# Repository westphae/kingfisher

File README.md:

# Kingfisher

Kingfisher is a flight data recorder for light aircraft. It runs on a
Raspberry Pi mounted in the cabin, reads sensors over IIO and ancillary
links, derives quantities like pressure altitude, magnetic declination,
and an AHRS-based attitude estimate, persists everything to a SQLite
flight database, and exposes a live cockpit UI over HTTP/WebSocket.

## Hardware

* **Main unit** mounted near the aircraft CG, inside the cabin.
  * Main controller is a `Raspberry Pi 5`.
  * Accel/gyro is a `ICM45686`.
  * GPS is a `NEO-M9N` attached via UART.
* **Pod unit** mounted out under the wing.
  * Pod controller is an `ESP32-C3-Mini-1`, variant `ESP32-C3FH4`.
  * Airspeed sensor is a `MS4525DO-DS5AI001DP`.
  * Static pressure (altimeter) sensor is a `BMP581`.
  * Magnetometer (compass) sensor is a `MMC5983MA`.

The pod is battery-powered and transmits sensor data to the main unit
wirelessly. See `internal/pod/` (Pi side) and `firmware/pod/` (ESP32
side) for the implementation.

## GPS

The `NEO-M9N` is wired to the Pi 5's GPIO UART (GPIO 14/15, header pins
8/10), enabled by `dtoverlay=uart0-pi5` in `/boot/firmware/config.txt`.

Kingfisher assumes the host wall clock is already sane. For offline operation,
discipline the Pi with `gpsd` + `chrony` first; see `docs/time-sync.md`.

**Pi 5 gotcha:** that UART is `/dev/ttyAMA0`, *not* `/dev/serial0`. On a
Pi 5 `/dev/serial0` points at the dedicated 3-pin debug-UART connector
(`ttyAMA10`), so gpsd must be told to use `/dev/ttyAMA0`. In
`/etc/default/gpsd`:

```
DEVICES="/dev/ttyAMA0"
GPSD_OPTIONS="-n -b -s 115200"
```

The `-b` (read-only) flag is deliberate. If you configured the M9N for 115200 baud
(saved to flash), you must also pass `-s 115200`; with `-b`, gpsd will not autobaud
and otherwise opens the port at 19200, which produces no fix and no TPV output. Left to manage the receiver,
gpsd subscribes a heavy set of UBX messages (NAV-SAT/SIG/POSECEF/…) that
saturate the link and drop the effective fix rate. Read-only keeps the
lean NAV-PVT-only stream the receiver is configured to emit, so we get a
clean 10 Hz.

For time discipline, prefer chrony's SOCK integration over SHM and keep
`chronyd` ahead of `gpsd` in the service order (and restart `gpsd` after any
`chronyd` restart). The repo-owned examples live in `deploy/time-sync/`. With PPS
wired, PPS disciplines the clock and the GPS serial source is marked `noselect`
(time-of-day only) — no per-receiver `offset` tuning is needed. See
`docs/time-sync.md`.

The receiver itself is configured once with `ubxtool` and the settings
are saved to its flash (they survive power-off). With gpsd running:

```bash
export UBXOPTS="-P 32.01"                      # M9N protocol version
ubxtool -z CFG-NAVSPG-DYNMODEL,7,7             # Airborne <2g (vs 0=portable)
ubxtool -z CFG-RATE-MEAS,100,7                 # 10 Hz (100 ms)
ubxtool -z CFG-RATE-NAV,1,7                    # 1 nav solution per measurement
```

To bump the link to 115200 and emit only UBX-NAV-PVT (do this with gpsd
*stopped*, talking to the port directly), set `CFG-UART1-BAUDRATE` to
`115200`, `CFG-MSGOUT-UBX_NAV_PVT_UART1` to `1`, and the other
`CFG-MSGOUT-UBX_NAV_*_UART1` items to `0`. The `,7` layer suffix writes
RAM+BBR+Flash so the config persists. The **Airborne dynamic model is the
most important setting** — the factory "portable" default filters motion
in ways that lag or drop fixes during climbs, descents, and turns.

### Rate (5 / 10 Hz)

The receiver always runs at 10 Hz; the GPS tab in the cockpit UI selects
the **recorded** rate (`rate_hz`, 5 or 10). Because gpsd is read-only,
kingfisher doesn't reconfigure the receiver — it decimates the 10 Hz
stream in software (`internal/gps`), publishing/recording every fix at
10 Hz or every other fix at 5 Hz. The setting persists in
`config.json` under `gps.rate_hz`.

### Timestamps (`ts_ns` vs fix time)

Each row in the `gps` table (and every other sensor table) has **`ts_ns`**: nanoseconds
on the Pi's disciplined wall clock. For GPS, **`ts_ns` is not the fix epoch** — it
is when kingfisher **received** the gpsd report. The receiver's fix time is stored
separately as the **`fix_time_unix_s`** column (typically **~600–700 ms earlier**
than `ts_ns` on this M9N + gpsd setup; that gap is receiver/pipeline lag, not clock
error).

For sensor fusion: align GPS with cabin IMU and pod data on **`ts_ns`**; use
**`fix_time_unix_s`** when you need GNSS solution time. Full per-source semantics
(buffered IIO, pod reconstruction, derived devices, fusion checklist) are in
**[`docs/timestamps.md`](docs/timestamps.md)**.

## Timestamps

All flight DB sensor tables store **`ts_ns`** (nanoseconds, Unix epoch) on the
Pi host wall clock (`CLOCK_REALTIME`), ideally GNSS-disciplined before recording.

| Source | `ts_ns` meaning (summary) |
|--------|---------------------------|
| Buffered IIO (ICM45686, …) | Kernel capture time when `current_timestamp_clock == realtime` |
| Polled IIO | Time when the periodic sysfs read completed |
| GPS | Pi time when the TPV was **received**; fix epoch is **`fix_time_unix_s`** |
| Pod (BMP581, MS4525, MMC5983) | Sample time reconstructed onto Pi clock from pod uptime + `age_us` |
| Derived (AHRS, press_alt, geo, compass) | Time when the value was **computed** (inputs may be slightly older) |

See **[`docs/timestamps.md`](docs/timestamps.md)** for measurement error vs true
sample time, GPS fusion guidance, and implementation references.

## Engine data (JPI EDM-930)

The EDM-930 is not on the live bus. After the flight, merge one download
into the flight SQLite. This installation records no altitude and no second
TIT, so the match is the GPS ground track. Format, refusal rules, and the
`jpi_edm930` columns are in [`docs/jpi-edm930.md`](docs/jpi-edm930.md).

```bash
uv run --project analysis python scripts/analyze_flights.py jpi \
  --jpi PATH/TO/FILE.JPI \
  --db PATH/TO/FLIGHT.sqlite \
  --flight N
```

That command is a dry run. Add `--apply` to write. Do not commit the `.jpi`
file or the flight database.

## Building

```
go build ./cmd/kingfisher
```

Pod firmware lives under `firmware/pod/`; see
[`firmware/pod/README.md`](firmware/pod/README.md) for the wiring,
toolchain, and flashing steps.

## Lint hook

Once per clone:

```bash
scripts/install-git-hooks.sh
```

That sets `git config core.hooksPath .githooks`. The pre-commit hook runs
`scripts/lint.sh`: `gofmt` on staged Go files, `scripts/check-wire.sh` when
`pod_wire/` or `internal/pod/wire/` is staged or those trees have unstaged
drift, and `golangci-lint` only if it is already on `PATH`. `gofmt` and the
wire check fail the commit. Unchecked `Close`, `Rollback`, and deadline
setters are ignored in `.golangci.yml`.

## Running

```
./kingfisher
```

Kingfisher listens on **`http_addr`** (default **`:8080`**) and is meant to sit
behind a reverse proxy on the aircraft LAN. Configuration lives in
`~/.config/kingfisher/config.json`.

### HTTPS with Caddy (recommended)

[Caddy](https://caddyserver.com/) terminates TLS on port **443**, redirects HTTP
port **80** to HTTPS, and reverse-proxies to kingfisher on `localhost:8080`
(including WebSocket traffic for the live cockpit and `/terminal`).

Example Caddyfile (also in **`deploy/caddy/Caddyfile`**). Adjust the hostname and
LAN IP for your Pi:

```caddyfile
https://kingfisher.lan, https://kingfisher, https://192.168.10.1, https://192.168.86.151, https://127.0.0.1 {
    tls internal
    reverse_proxy localhost:8080
}

http://kingfisher.lan, http://kingfisher, http://192.168.10.1, http://192.168.86.151, http://127.0.0.1 {
    redir https://{host}{uri} permanent
}
```

`tls internal` uses a **local certificate authority** managed by Caddy — fine for
a private LAN; not a public-trusted cert.

**Install on Debian / Raspberry Pi OS** (official apt repo):

```bash
sudo apt install -y debian-keyring debian-archive-keyring apt-transport-https curl
curl -1sLf 'https://dl.cloudsmith.io/public/caddy/stable/gpg.key' \
  | sudo gpg --dearmor -o /usr/share/keyrings/caddy-stable-archive-keyring.gpg
curl -1sLf 'https://dl.cloudsmith.io/public/caddy/stable/debian.deb.txt' \
  | sudo tee /etc/apt/sources.list.d/caddy-stable.list
sudo chmod o+r /usr/share/keyrings/caddy-stable-archive-keyring.gpg \
  /etc/apt/sources.list.d/caddy-stable.list
sudo apt update && sudo apt install -y caddy
sudo cp deploy/caddy/Caddyfile /etc/caddy/Caddyfile
sudo caddy validate --config /etc/caddy/Caddyfile
sudo systemctl enable --now caddy
```

Keep kingfisher on the loopback port only:

```json
"http_addr": ":8080"
```

**Trust the CA**

On the Pi (so curl and local browsers trust HTTPS):

```bash
sudo caddy trust
```

On laptops, phones, and tablets, install Caddy's root certificate once. After
Caddy has started at least once, the file is usually:

```text
/var/lib/caddy/.local/share/caddy/pki/authorities/local/root.crt
```

Copy it to the device and add it to the system/browser trust store (or use
`sudo caddy trust` on each Linux machine). Until then, browsers show a
certificate warning — you can proceed for testing, but trusting the CA removes
the nag and enables secure-context APIs (clipboard, etc.) over HTTPS.

Open the cockpit at **`https://<pi-hostname-or-ip>/`** (port 443; HTTP on port 80
redirects automatically).

### EFB apps (ForeFlight, iFlyEFB)

Kingfisher can broadcast **Stratux-compatible GDL90** over UDP port **4000** so
tablets on the Pi access point receive GPS position and AHRS attitude without a
separate Stratux box. Enable in `config.json`:

```json
"gdl90": {
  "enabled": true,
  "static_ips": ["192.168.10.141", "192.168.10.40"]
}
```

On the Pi AP (NetworkManager + dnsmasq), list each tablet’s reserved IP in
`static_ips` — see **`deploy/efb/ap-setup.md`** for DHCP reservations, MAC
privacy settings, and verification.

**ForeFlight:** connect to the Pi Wi‑Fi → *More* → *Devices* → enable GDL90 at
**`192.168.10.1`**.

**iFlyEFB:** *Menu* → *About* → *Connected Devices* → Stratux/FlightBox;
*Setup* → *ADS-B* → Stratux/Flightbox (manual). Expect **GPS Data Only**.

Requires `ahrs.enabled` for attitude. Traffic and weather are not sent (no ADS-B
receiver). Check `/api/status` → `gdl90` for client count and last send time;
`tcpdump -i wlan0 udp port 4000` should show steady packets when an EFB is
connected.

### systemd user service (boot)

Kingfisher is normally run as your Pi login user (IIO device access, config under
`~/.config/kingfisher/`, flight DBs under `~/kingfisher/flights`). A **systemd user
unit** starts it at boot without keeping an SSH session open.

**Prerequisites:** gpsd and chrony configured per **`docs/time-sync.md`**. If you
use Caddy for HTTPS, enable **`caddy.service`** separately (system unit); start
kingfisher first so the reverse proxy has a backend on `:8080`.

1. **Install the binary** with `go install` (default: `$(go env GOPATH)/bin`, usually
   `~/go/bin`; override with `GOBIN` if you use it):

   ```bash
   cd ~/go/src/github.com/westphae/kingfisher
   go install ./cmd/kingfisher
   ```

2. **Install the user unit** from the repo example (path must match step 1):

   ```bash
   mkdir -p ~/.config/systemd/user
   bin="$(go env GOBIN)"
   [ -z "$bin" ] && bin="$(go env GOPATH)/bin"
   sed "s|__KINGFISHER_BIN__|$bin/kingfisher|g" \
     deploy/systemd/kingfisher.service.example \
     > ~/.config/systemd/user/kingfisher.service
   ```

3. **Enable linger** so the user service starts at boot (not only after login):

   ```bash
   sudo loginctl enable-linger "$USER"
   loginctl show-user "$USER" -p Linger   # expect Linger=yes
   ```

4. **Enable and start:**

   ```bash
   systemctl --user daemon-reload
   systemctl --user enable --now kingfisher.service
   ```

5. **Check status and logs:**

   ```bash
   systemctl --user status kingfisher.service
   journalctl --user-unit=kingfisher.service -f
   curl -s http://127.0.0.1:8080/api/status | head
   ```

   Use **`--user-unit`** (not `journalctl --user`): on Raspberry Pi OS the user
   manager logs to the **system** journal; there is no separate per-user journal
   file under `/run/user/$UID/journal`, so `journalctl --user` shows nothing even
   though `systemctl --user status` does.

The unit starts kingfisher **immediately** — there is no chrony pre-wait (the
old `kingfisher-prestart.sh` gate is retired). The UI and recording come up in
seconds on the RTC clock:

| Situation | Behavior |
|-----------|----------|
| **RTC sane (normal)** | Timestamp-named flight DB; red cockpit banner until chrony locks |
| **Any chrony step/slew ≥ 20 ms** | Row in the DB's `clock_offsets` table (see `docs/timestamps.md`) |
| **RTC dead (clock reads 1970)** | DB named `unsynced_NNNN_<tail>.db`; renamed at close once true time is known |

Startup metadata, the `clock_offsets` mapping table, and the cockpit clock
badge/banner record discipline state. `RestartSec=30` retries a failed main
process.

**After upgrading:** `go install ./cmd/kingfisher`, then
`systemctl --user restart kingfisher.service`.

**Stop/disable:**

```bash
systemctl --user disable --now kingfisher.service
```

Example unit file: **`deploy/systemd/kingfisher.service.example`**.

### Browser terminal (optional)

Kingfisher can expose a full-screen web terminal at **`/terminal`** (footer link
on the cockpit page). It is **disabled by default**; enable in `config.json`:

```json
"terminal": {
  "enabled": true,
  "user": "eric",
  "authorized_keys": [
    "ssh-ed25519 AAAA... kingfisher-terminal"
  ],
  "allow_password": false,
  "session_timeout_min": 480,
  "max_sessions": 2
}
```

**Public-key login (recommended):** put one or more OpenSSH `authorized_keys` lines in
`authorized_keys` and set `user` to the Unix account the shell should run as. The
browser signs a one-time challenge with a private key stored locally (generate in
the terminal UI, or import an unencrypted Ed25519 `id_ed25519`). Your password is
never sent. Set `"allow_password": true` to keep PAM login as a fallback.

**Password login:** when `authorized_keys` is omitted, login uses **Linux PAM**
(same username/password as SSH). The shell runs as the authenticated user when
kingfisher runs as that user; logging in as a different user requires root or
`cap_setuid` on the kingfisher binary.

**Security:** with Caddy **`tls internal`** in front (see above), terminal traffic
including WebSockets is encrypted on the LAN. Without HTTPS, password login sends
credentials in cleartext; public-key login avoids sending passwords but session
cookies and shell I/O are still visible on the wire.

Building on Linux requires **`libpam0g-dev`** for CGO (`apt install libpam0g-dev`).

If you want DB filenames, session start times, and buffered IIO timestamps to be
meaningful immediately after boot, start kingfisher only after GNSS time sync is
healthy. `docs/time-sync.md` includes a `chronyc waitsync` systemd pattern and a
verification checklist. Per-table **`ts_ns`** semantics and sensor-fusion usage
(including GPS **`fix_time_unix_s`**) are documented in **`docs/timestamps.md`**.

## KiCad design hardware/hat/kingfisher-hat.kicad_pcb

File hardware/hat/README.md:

# Kingfisher Sensor HAT (rev 0.3)

Custom HAT for the extra-tall GPIO header above the M.2 HAT+. It replaces the
cabin SparkFun NEO-M9N and ICM-45686 breakouts. The schematic netlist is
checked. The board is routed on JLCPCB stackup JLC04161H-7628. Gerbers
and drills are in `fab/`. Confirm header engagement, the CR2032 against the
lid, and that the GNSS antenna is active before ordering.

| Ref | Part | Role |
|-----|------|------|
| U1 | ICM-45686 | Cabin IMU, I²C `0x68`, INT1 → GPIO17 |
| U2 | BMP581 | Extra cabin baro, I²C `0x47` |
| U3 | AP2112K-3.3 | 5 V → 3.3 V for the GPS only |
| U4 | NEO-M9N | GNSS, UART0 + PPS on GPIO18 |
| U5 | RV-3028-C7 | I²C RTC at `0x52` |
| U6 | LM4040-3.0 | 3.00 V clamp for the ML414H charge |
| BT1 | CR2032, Keystone 3002 | Replaceable cell for the RTC `VBACKUP` only |
| BT2 | ML414H | Soldered rechargeable cell on GPS `V_BCKP` |
| D1 | PMEG4005EJ | Blocks the ML414H from the reference |
| D2 | Green LED | `+3V3_GPS` through 1 kΩ |
| D3 | ESD0P2RF | 0.2 pF ESD diode, RF to ground at the U.FL |
| L1 | LQG15HS27NJ02D | 27 nH antenna-bias choke |
| J1 | 2×20 socket, bottom | Mates the extended Pi header. Do not move it |
| J2 | U.FL | Antenna. 0.32 mm microstrip plus the bias-T stub |
| J3 | 1×5 header | X1200 harness: +3V3, GND, SDA, SCL, GPIO6 |

Outline is the official Pi HAT (65 × 56.5 mm, M2.5 on 58 × 49 mm).

The GPS circuit follows UBX-19014285 and UBX-19014286: `V_USB` grounded,
UART pull-up on `D_SEL`, 33 Ω on TX/RX, ML414H directly on `V_BCKP` charged
through an LM4040-3.0 and 34 kΩ, and a 27 nH / 100 nF bias-T into the
antenna. The CR2032 does not back up the GPS and has no charge path. There
is no UPS on this board. See [docs/DESIGN.md](docs/DESIGN.md).

## Open in KiCad

KiCad 9 (generated against 9.0.2).

```bash
kicad hardware/hat/kingfisher-hat.kicad_pro
```

Libraries:

- `libs/Kingfisher.kicad_sym` — ICM-45686, BMP581, NEO-M9N
- `libs/Kingfisher.pretty` — ICM-45686 (TDK pin numbers), BMP581, ML414H

Regenerate with system Python, not a uv venv. `pcbnew` comes from
`python3-pcbnew`.

```bash
python3 hardware/hat/scripts/build_libs.py
python3 hardware/hat/scripts/build_sch.py
kicad-cli sch export netlist -o /tmp/kingfisher-hat.net hardware/hat/kingfisher-hat.kicad_sch
python3 hardware/hat/scripts/check_netlist.py /tmp/kingfisher-hat.net
python3 hardware/hat/scripts/place_pcb.py
python3 hardware/hat/scripts/route_pcb.py
```

`check_netlist.py` is the schematic check. It passed for rev 0.3 (69 nets).
`place_pcb.py` keeps the template socket and mounting holes and deletes
tracks. `route_pcb.py` restores the route and the 4-layer stackup.

## Status

Done:

- Schematic for the GPS replica, TDK IMU land, BMP581, RV-3028, both backup
  cells, X1200 header, test points, and the GPS power LED
- Netlist check against datasheet pin numbers
- Parts placed on the HAT outline, clear of the notch, the slot, the mounting
  holes, and the header
- Routed, including the 0.32 mm U.FL microstrip (bare Z0 about 50.2 Ω at the
  pressed 7.1 mil / Er 4.4 height). Soldermask pulls that down about 1–2 Ω
- JLC04161H-7628 stackup filled in. Error-level DRC is clean
- Gerbers and drills in `fab/`

Still to confirm on the aircraft, and still open in software:

- Female-header engagement, lid clearance over the CR2032, pin 1 against the
  real extender, and whether the GNSS antenna is active
- `i2c-rtc` for the RV-3028, a cabin BMP581 reader, and an AHRS mount matrix
  measured from this board's silk

## Attribution

- Outline and GPIO socket: KiCad Raspberry Pi HAT template
- BMP581 pads: SparkFun Qwiic BMP581 hardware, CC-BY-SA 4.0
- ML414H pads and the GPS power circuit: SparkFun NEO-M9N SMA / SparkFun-Batteries
- NEO-M9N symbol: derived from the KiCad `NEO-M8N` symbol
- ICM-45686 pad centers: IPC LGA-14. Pin numbers and axes: TDK DS-000577

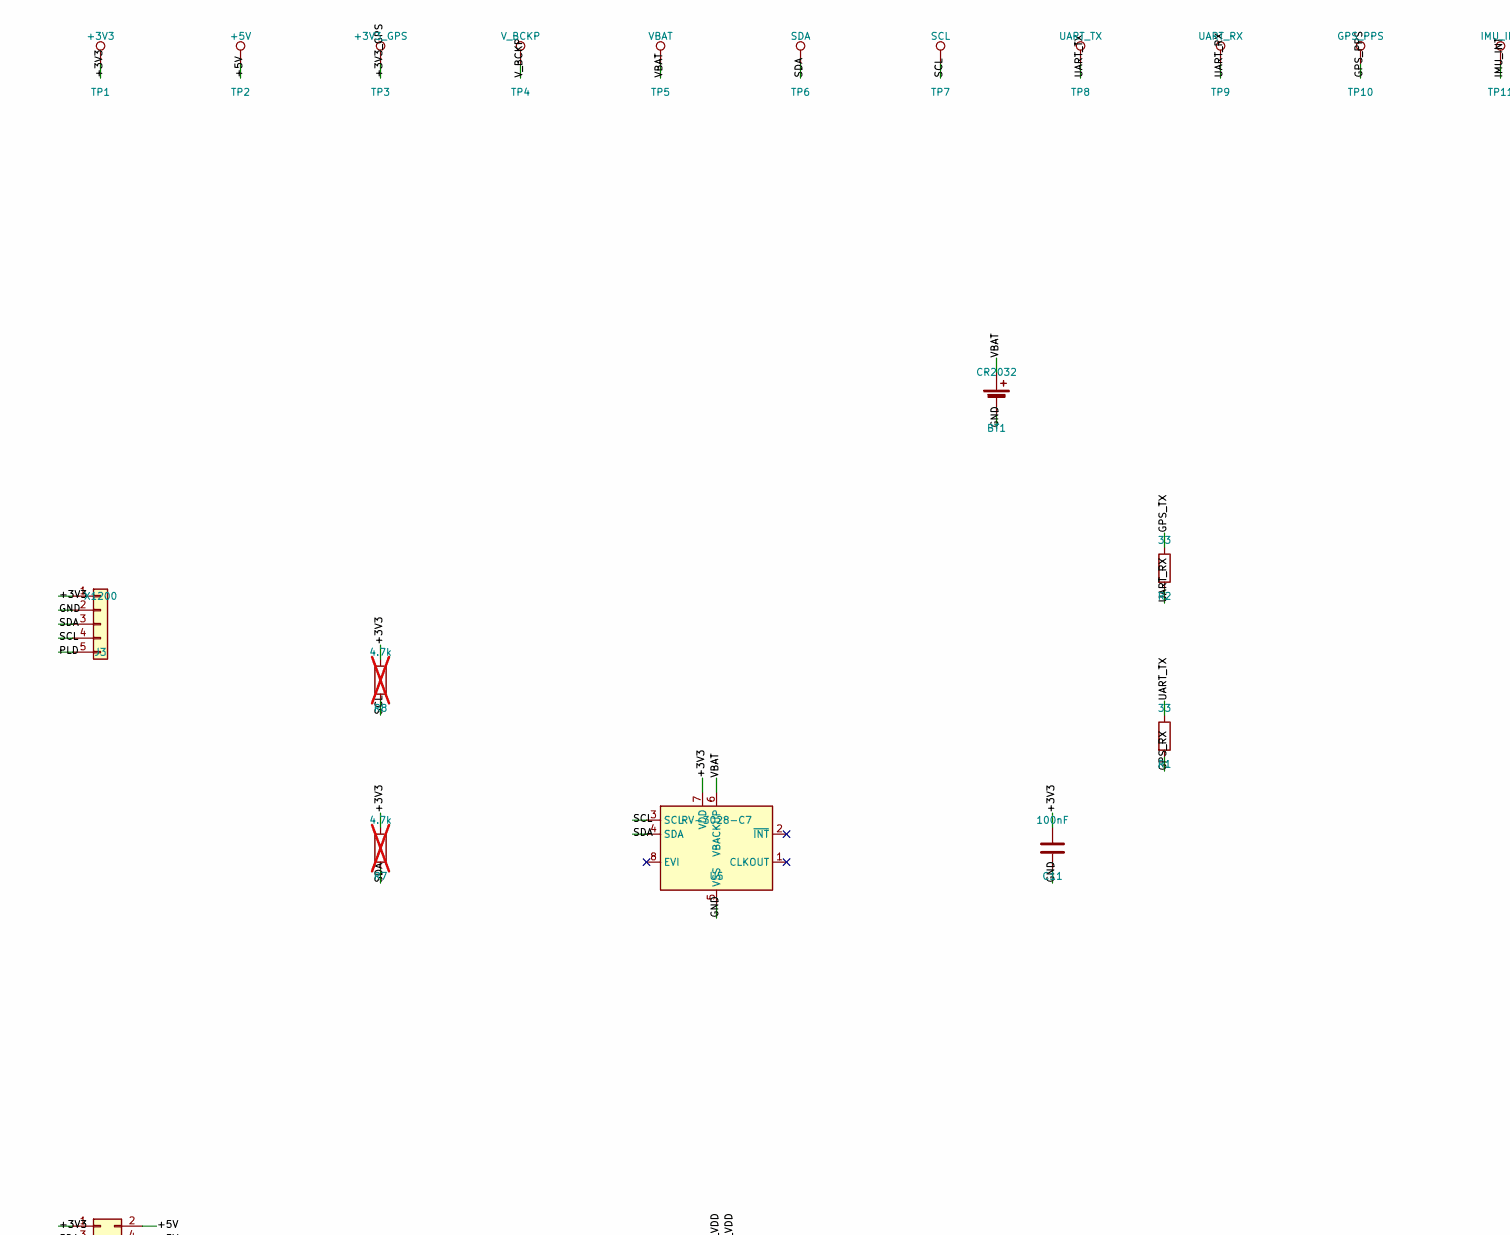
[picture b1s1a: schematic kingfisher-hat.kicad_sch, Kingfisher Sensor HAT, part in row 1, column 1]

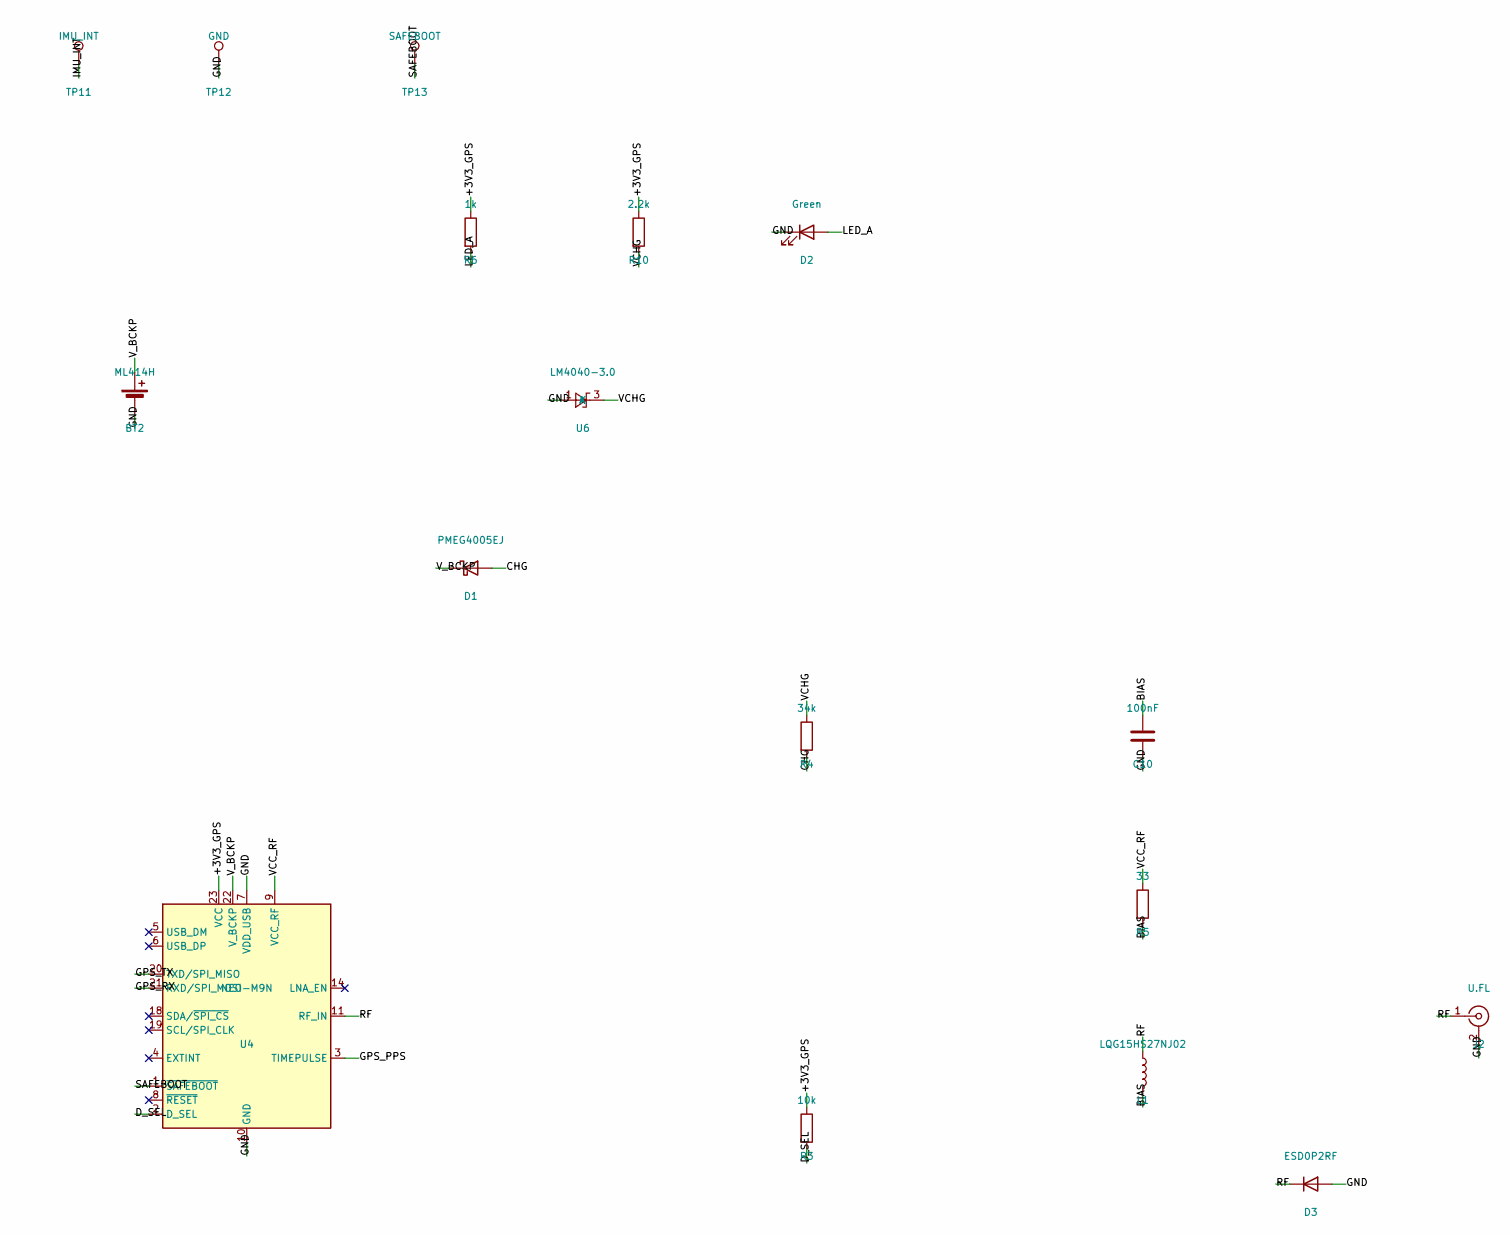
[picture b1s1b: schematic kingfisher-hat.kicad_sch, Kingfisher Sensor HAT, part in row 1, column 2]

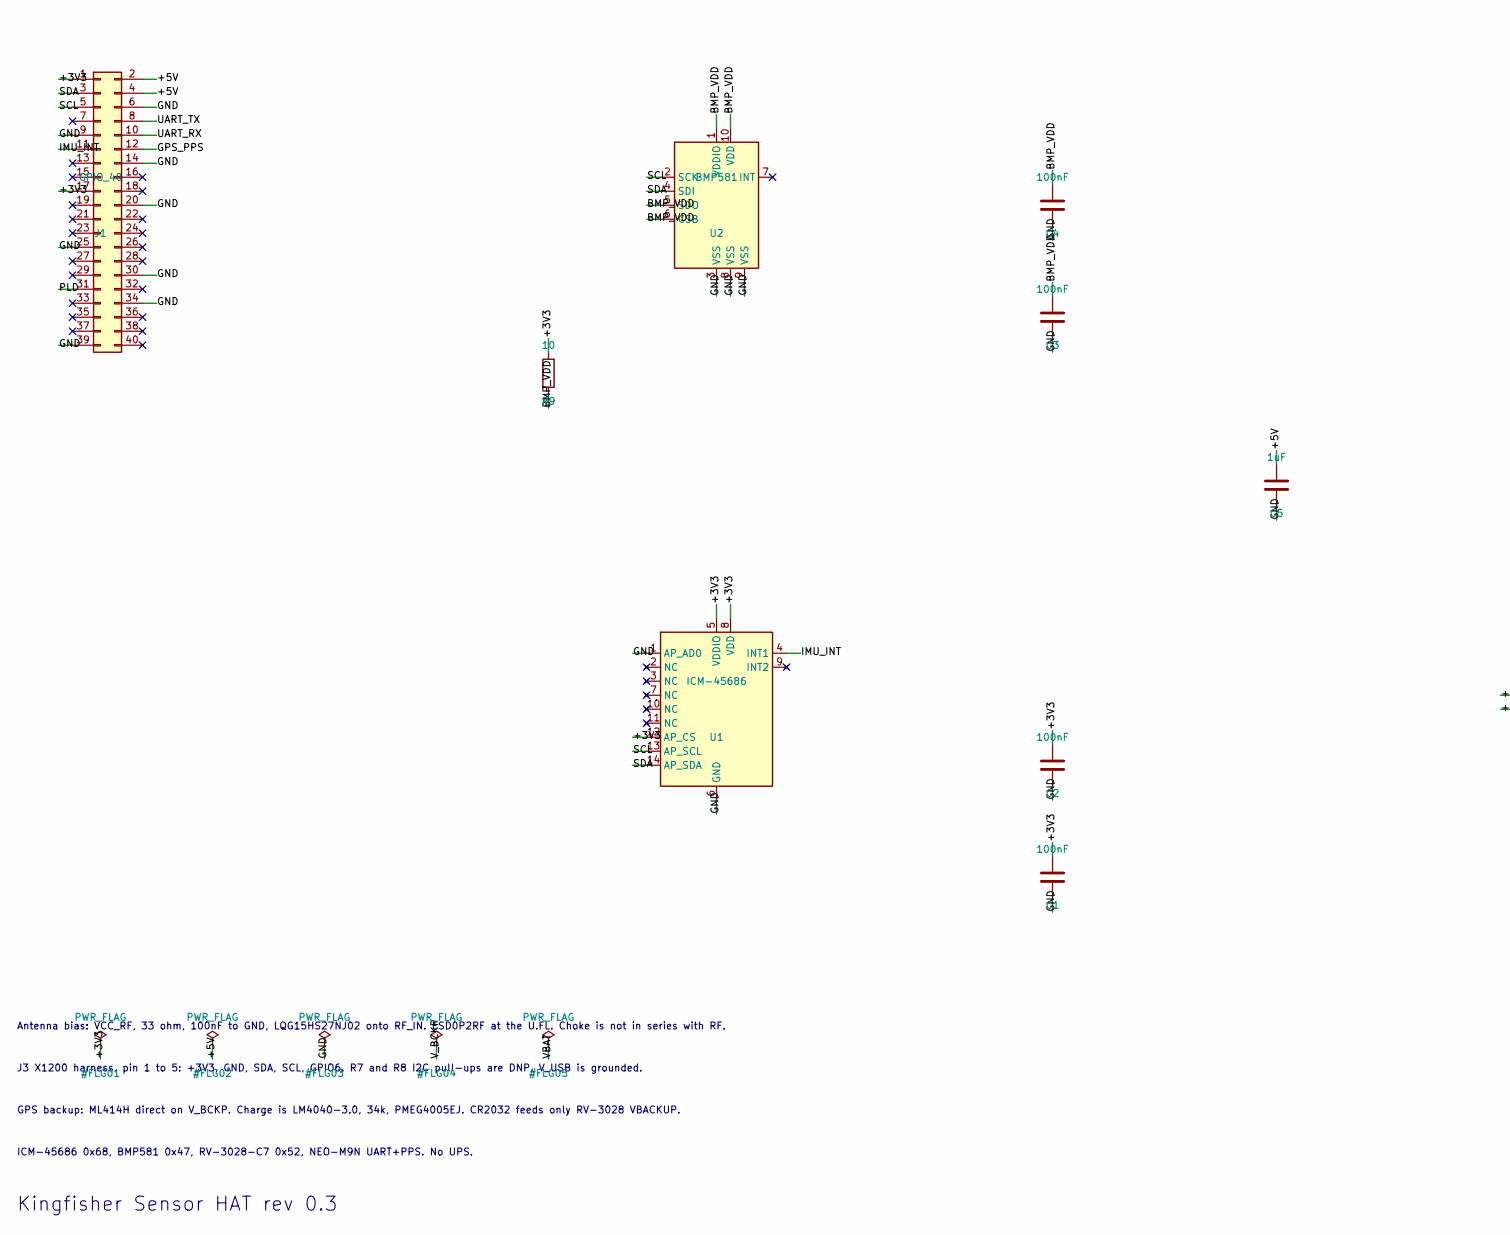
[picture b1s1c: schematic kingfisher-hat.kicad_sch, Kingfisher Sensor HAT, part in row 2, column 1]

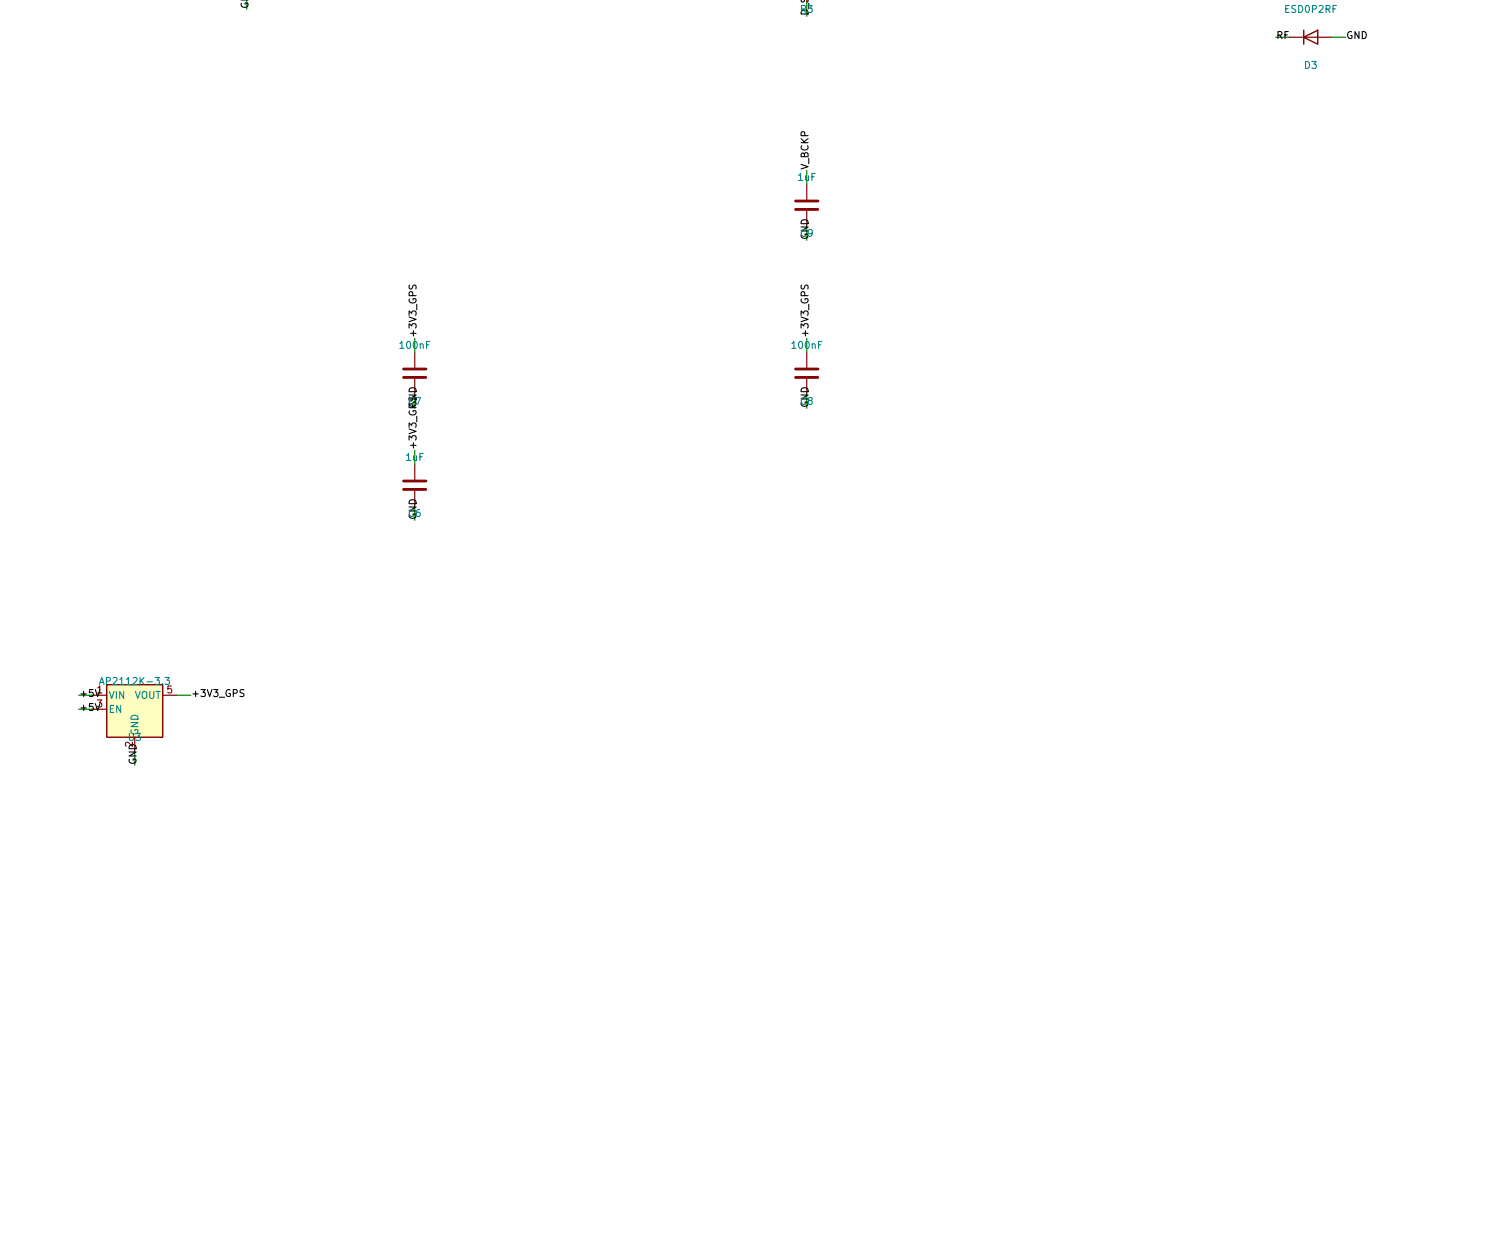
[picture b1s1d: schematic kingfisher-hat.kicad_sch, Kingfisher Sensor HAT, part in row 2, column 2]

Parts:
BT1: CR2032; BatteryHolder_Keystone_3002_1x2032
BT2: ML414H
C1, C2, C3, C4, C7, C8, C10, C11: 100nF; C_0402_1005Metric
C5, C6, C9: 1uF; C_0603_1608Metric
D1: PMEG4005EJ; D_SOD-323F
D2: Green; LED_0603_1608Metric
D3: ESD0P2RF; D_SOD-882
J1: GPIO_40; PinSocket_2x20_P2.54mm_Vertical
J2: U.FL; U.FL_Hirose_U.FL-R-SMT-1_Vertical
J3: X1200; PinHeader_1x05_P2.54mm_Horizontal
L1: LQG15HS27NJ02; L_0402_1005Metric
R1, R2: 33; R_0603_1608Metric
R3: 10k; R_0402_1005Metric
R4: 34k; R_0603_1608Metric
R5: 33; R_0402_1005Metric
R6: 1k; R_0603_1608Metric
R7, R8: 4.7k; R_0402_1005Metric; not fitted
R9: 10; R_0402_1005Metric
R10: 2.2k; R_0402_1005Metric
TP1: +3V3; TestPoint_Pad_D1.5mm
TP2: +5V; TestPoint_Pad_D1.5mm
TP3: +3V3_GPS; TestPoint_Pad_D1.5mm
TP4: V_BCKP; TestPoint_Pad_D1.5mm
TP5: VBAT; TestPoint_Pad_D1.5mm
TP6: SDA; TestPoint_Pad_D1.5mm
TP7: SCL; TestPoint_Pad_D1.5mm
TP8: UART_TX; TestPoint_Pad_D1.5mm
TP9: UART_RX; TestPoint_Pad_D1.5mm
TP10: GPS_PPS; TestPoint_Pad_D1.5mm
TP11: IMU_INT; TestPoint_Pad_D1.5mm
TP12: GND; TestPoint_Pad_D1.5mm
TP13: SAFEBOOT; TestPoint_Pad_D1.5mm
U1: ICM-45686
U2: BMP581
U3: AP2112K-3.3; SOT-23-5_JLC
U4: NEO-M9N; ublox_NEO
U5: RV-3028-C7; RV3028-C7_JLC
U6: LM4040-3.0; SOT-353_SC-70-5_JLC

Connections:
+3V3: C1.1, C2.1, C11.1, J1.1, J1.17, J3.1, R7.1, R8.1, R9.1, TP1.1, U1.5 (VDDIO), U1.8 (VDD), U1.12 (AP_CS), U5.7 (VDD)
+3V3_GPS: C6.1, C7.1, C8.1, R3.1, R6.1, R10.1, TP3.1, U3.5 (VOUT), U4.23 (VCC)
+5V: C5.1, J1.2, J1.4, TP2.1, U3.1 (VIN), U3.3 (EN)
BIAS: C10.1, L1.2, R5.2
BMP_VDD: C3.1, C4.1, R9.2, U2.1 (VDDIO), U2.5 (SDO), U2.6 (CSB), U2.10 (VDD)
CHG: D1.2 (A), R4.2
D_SEL: R3.2, U4.2 (D_SEL)
GND: BT1.2 (-), BT2.2 (-), C1.2, C2.2, C3.2, C4.2, C5.2, C6.2, C7.2, C8.2, C9.2, C10.2, C11.2, D2.1 (K), D3.2 (A), J1.6, J1.9, J1.14, J1.20, J1.25, J1.30, J1.34, J1.39, J2.2 (Ext), J3.2, TP12.1, U1.1 (AP_AD0), U1.6 (GND), U2.3 (VSS), U2.8 (VSS), U2.9 (VSS), U3.2 (GND), U4.7 (VDD_USB), U4.10 (GND), U4.12 (GND), U4.13 (GND), U4.24 (GND), U5.5 (VSS), U6.1 (A)
GPS_PPS: J1.12, TP10.1, U4.3 (TIMEPULSE)
GPS_RX: R1.2, U4.21 (RXD/SPI_MOSI)
GPS_TX: R2.1, U4.20 (TXD/SPI_MISO)
IMU_INT: J1.11, TP11.1, U1.4 (INT1)
LED_A: D2.2 (A), R6.2
PLD: J1.31, J3.5
RF: D3.1 (K), J2.1 (In), L1.1, U4.11 (RF_IN)
SAFEBOOT: TP13.1, U4.1 (~SAFEBOOT)
SCL: J1.5, J3.4, R8.2, TP7.1, U1.13 (AP_SCL), U2.2 (SCK), U5.3 (SCL)
SDA: J1.3, J3.3, R7.2, TP6.1, U1.14 (AP_SDA), U2.4 (SDI), U5.4 (SDA)
UART_RX: J1.10, R2.2, TP9.1
UART_TX: J1.8, R1.1, TP8.1
VBAT: BT1.1 (+), TP5.1, U5.6 (VBACKUP)
VCC_RF: R5.1, U4.9 (VCC_RF)
VCHG: R4.1, R10.2, U6.3 (K)
V_BCKP: BT2.1 (+), C9.1, D1.1 (K), TP4.1, U4.22 (V_BCKP)

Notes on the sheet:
Kingfisher Sensor HAT rev 0.3
ICM-45686 0x68, BMP581 0x47, RV-3028-C7 0x52, NEO-M9N UART+PPS. No UPS.
GPS backup: ML414H direct on V_BCKP. Charge is LM4040-3.0, 34k, PMEG4005EJ. CR2032 feeds only RV-3028 VBACKUP.
J3 X1200 harness, pin 1 to 5: +3V3, GND, SDA, SCL, GPIO6. R7 and R8 I2C pull-ups are DNP. V_USB is grounded.
Antenna bias: VCC_RF, 33 ohm, 100nF to GND, LQG15HS27NJ02 onto RF_IN. ESD0P2RF at the U.FL. Choke is not in series with RF.

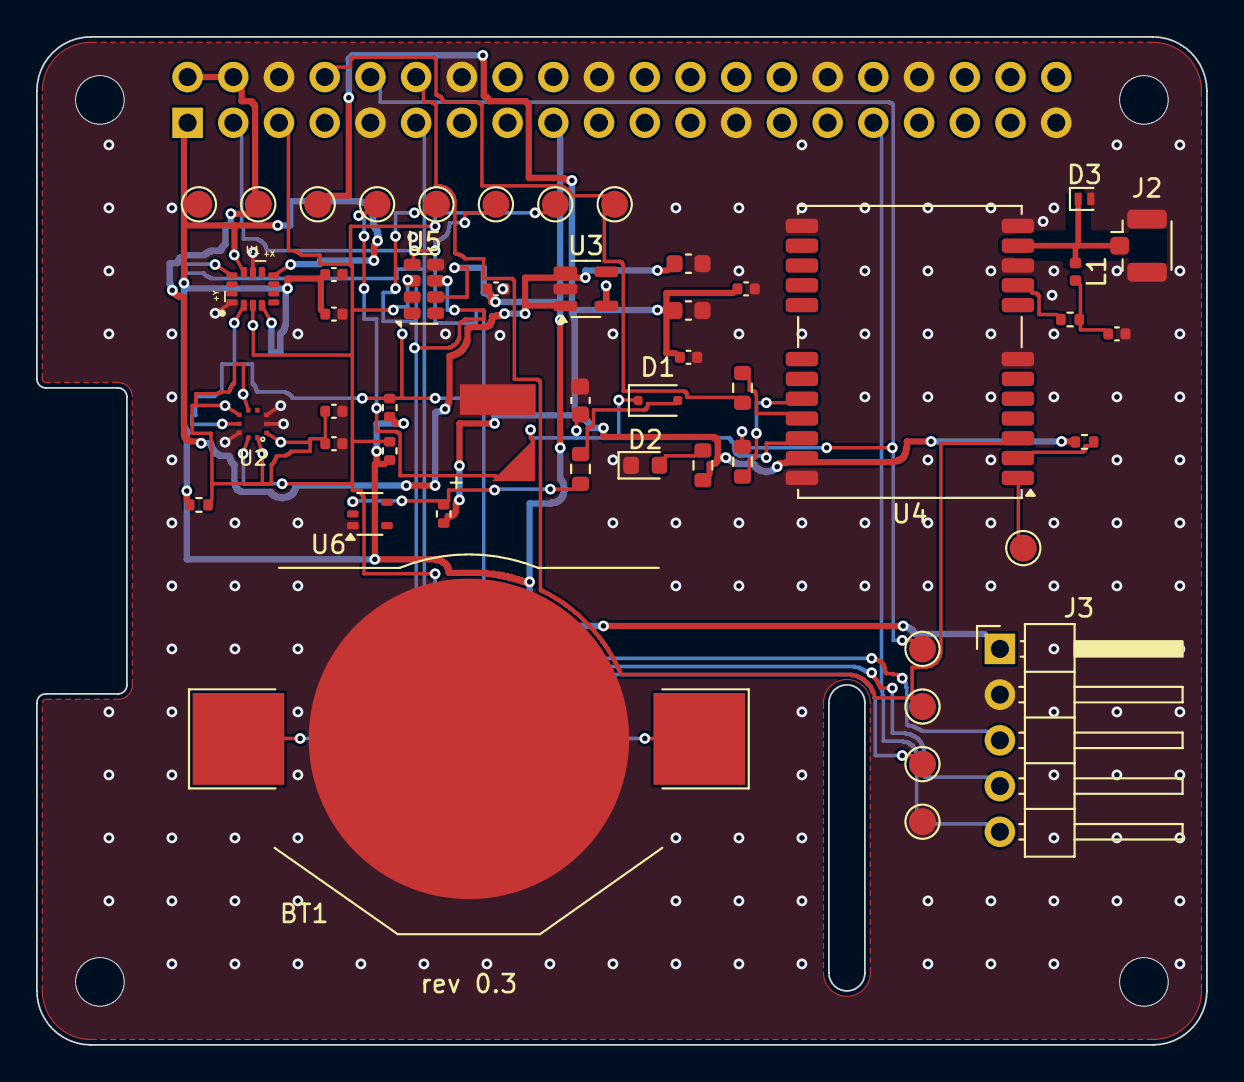
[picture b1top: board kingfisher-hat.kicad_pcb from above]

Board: 4 copper layers, 65.0 x 56.0 mm, 53 parts (1 on the bottom side), 24 nets.

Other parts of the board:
MH1, MH2, MH3, MH4: MountingHole_2.7mm_M2.5

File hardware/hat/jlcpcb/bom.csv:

Comment,Designator,Footprint,JLCPCB Part #
100nF 16V X7R ±10% 0402,"C1,C2,C3,C4,C7,C8,C10,C11",0402,C1525
1uF 50V X5R ±10% 0603,"C5,C6,C9",0603,C15849
33Ω ±1% 0603,"R1,R2",0603,C23140
33Ω ±1% 0402,R5,0402,C25105
10kΩ ±1% 0402,R3,0402,C25744
34.0kΩ ±1% 0603,R4,0603,C843946
2.2kΩ ±1% 0402,R10,0402,C25879
10Ω ±1% 0402,R9,0402,C25077
1kΩ ±1% 0603,R6,0603,C21190
Yellow-green LED 0603 LTST-C190KGKT cathode on pin 1,D2,LED-0603,C125094
PMEG4005EJ SOD-323F,D1,SOD-323F,C426868
Bidirectional ESD DFN1006-2 Cd max 0.5pF 5V,D3,SOD-882,
LQG15HS27NJ02D,L1,0402,C12669
LM4040C30IDCKR,U6,SC-70-5,C701882
AP2112K-3.3TRG1,U3,SOT-23-5,C51118
ICM-45686,U1,LGA-14,C22459454
Bosch BMP581 LGA-10 2.0x2.0,U2,LGA-10,C5362283
RV-3028-C7,U5,DFN-8,C2829066
u-blox NEO-M9N-00B,U4,NEO-M9N,
Seiko ML414H-IV01E,BT2,ML414H,
Keystone 3002 SMT 20mm coin clip,BT1,Keystone-3002,C5503436
Hirose U.FL-R-SMT-1,J2,U.FL,C598199
Female socket 2x20 2.54mm,J1,PinSocket-2x20,
Pin header 1x5 2.54mm right-angle,J3,PinHeader-1x5,C3040097

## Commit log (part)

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2026-05-22 Add AGENTS.md with Cursor Cloud development instructions
2026-05-22 Apply gofmt -w to existing source
    Whitespace-only changes from running gofmt over the eight files that
    were previously slightly off (struct field alignment and one wrapped
    expression). No behaviour change; prepares the tree for a gofmt
    formatter to be wired into the lint setup.
2026-05-22 Apply cargo fmt to pod_wire and firmware/pod
    Whitespace-only changes from running rustfmt over both crates. No
    behaviour change; prepares the tree for cargo fmt --check to be wired
    into the lint setup.
2026-05-22 chore(lint): add golangci-lint config, Makefile, and CI workflow
    Add .golangci.yml (standard linters + gofmt/goimports formatters),
    Makefile targets for lint/fmt, and a GitHub Actions workflow that runs
    golangci-lint and go vet on Go plus rustfmt/clippy on pod_wire.
2026-05-22 fix: satisfy golangci-lint and format checks
    Check Close/Rollback/deadline errors explicitly or ignore with _.
    Use defer Rollback/Close patterns in store transactions.
    Remove unused canonicalPodAttrKey; cover svarint with a unit test.
    Run gofmt on Go sources and rustfmt on pod_wire.
2026-05-22 Add Go + Rust linting infrastructure
    Set up a single Makefile that drives both languages:
    make lint full lint (Go + Rust)
    make lint-go golangci-lint run ./...
    make lint-rust cargo fmt --check + clippy on pod_wire
    (firmware/pod needs the esp toolchain; available via
    make lint-firmware on a host that has it)
2026-05-31 Add preliminary enclosures shape files for 3D printing. Unprinted for now.
2026-06-16 Ad cursor memory about ro root

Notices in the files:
parts and their libraries:
Bosch BMP581 LGA-10 2.0x2.0mm; pad layout adapted from SparkFun Qwiic BMP581 (CC-BY-SA 4.0)
